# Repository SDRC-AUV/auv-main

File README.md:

auv-main
========

Central repository for documentation and useful links related to the AUV.

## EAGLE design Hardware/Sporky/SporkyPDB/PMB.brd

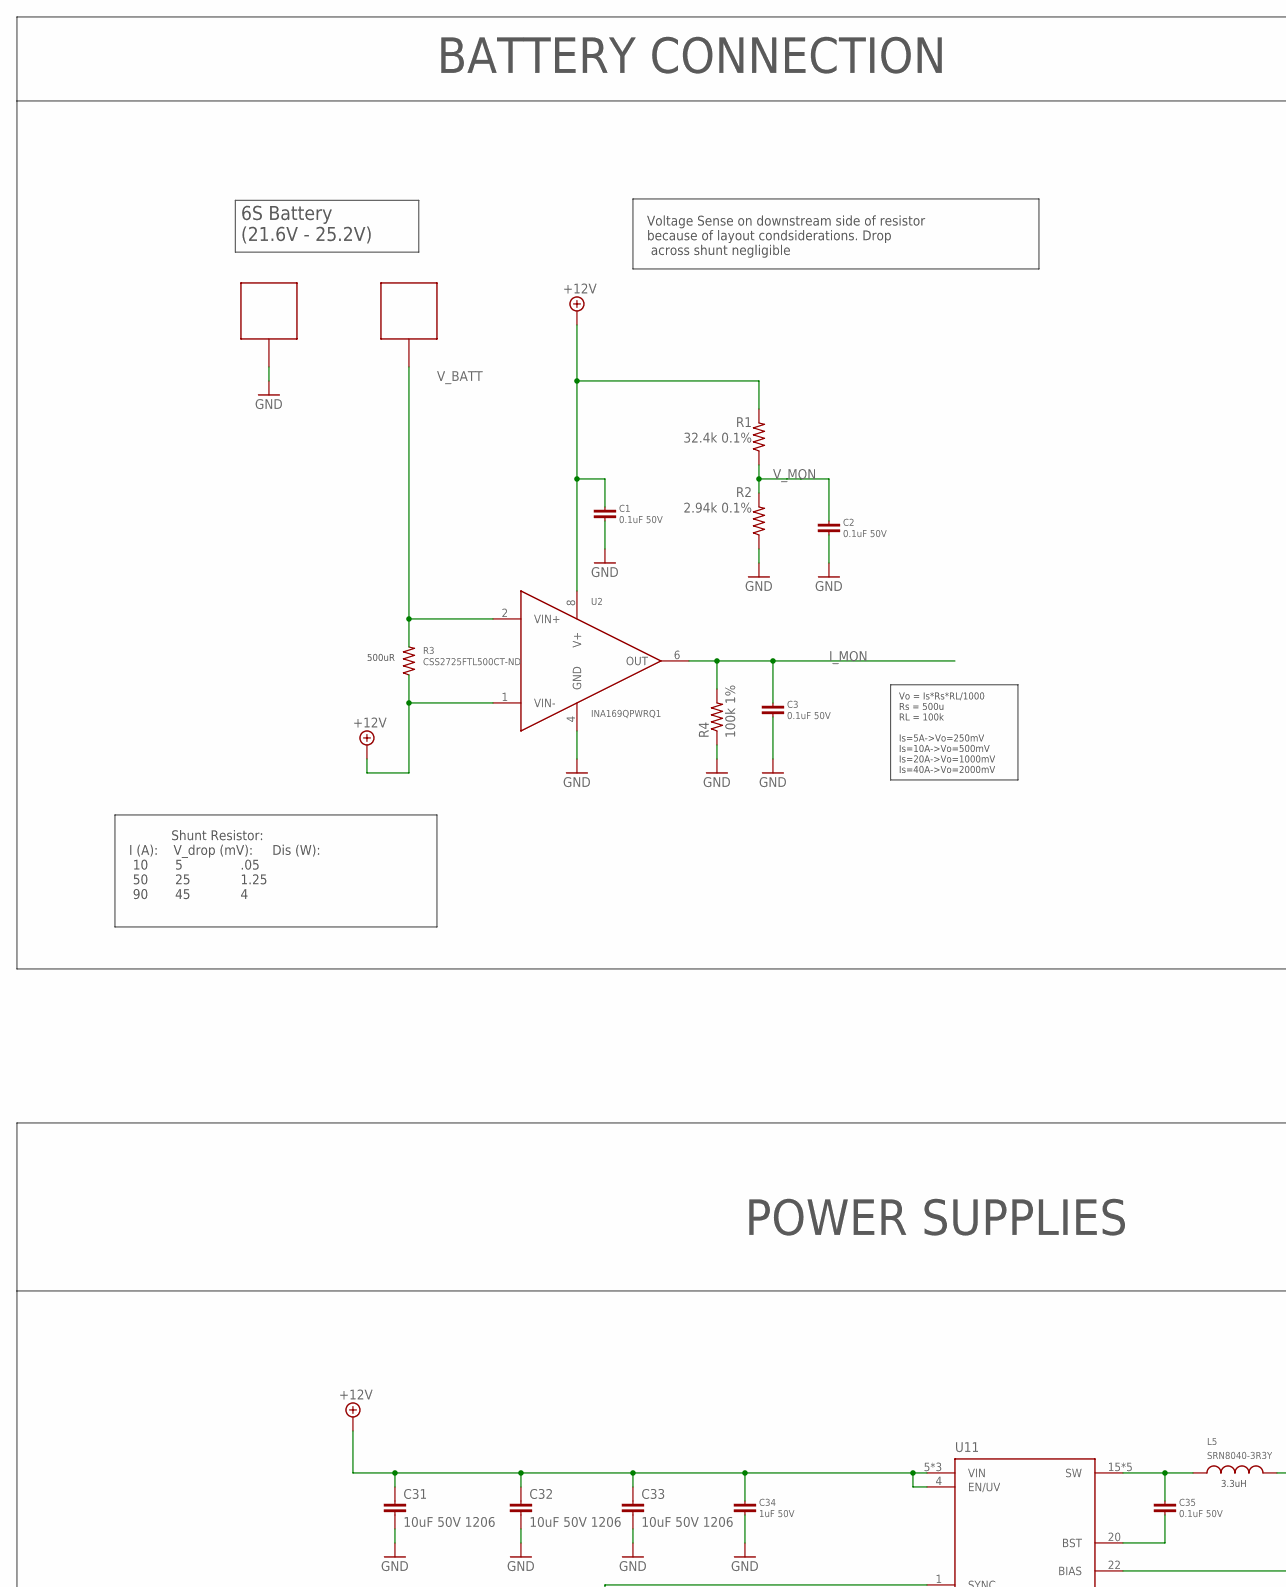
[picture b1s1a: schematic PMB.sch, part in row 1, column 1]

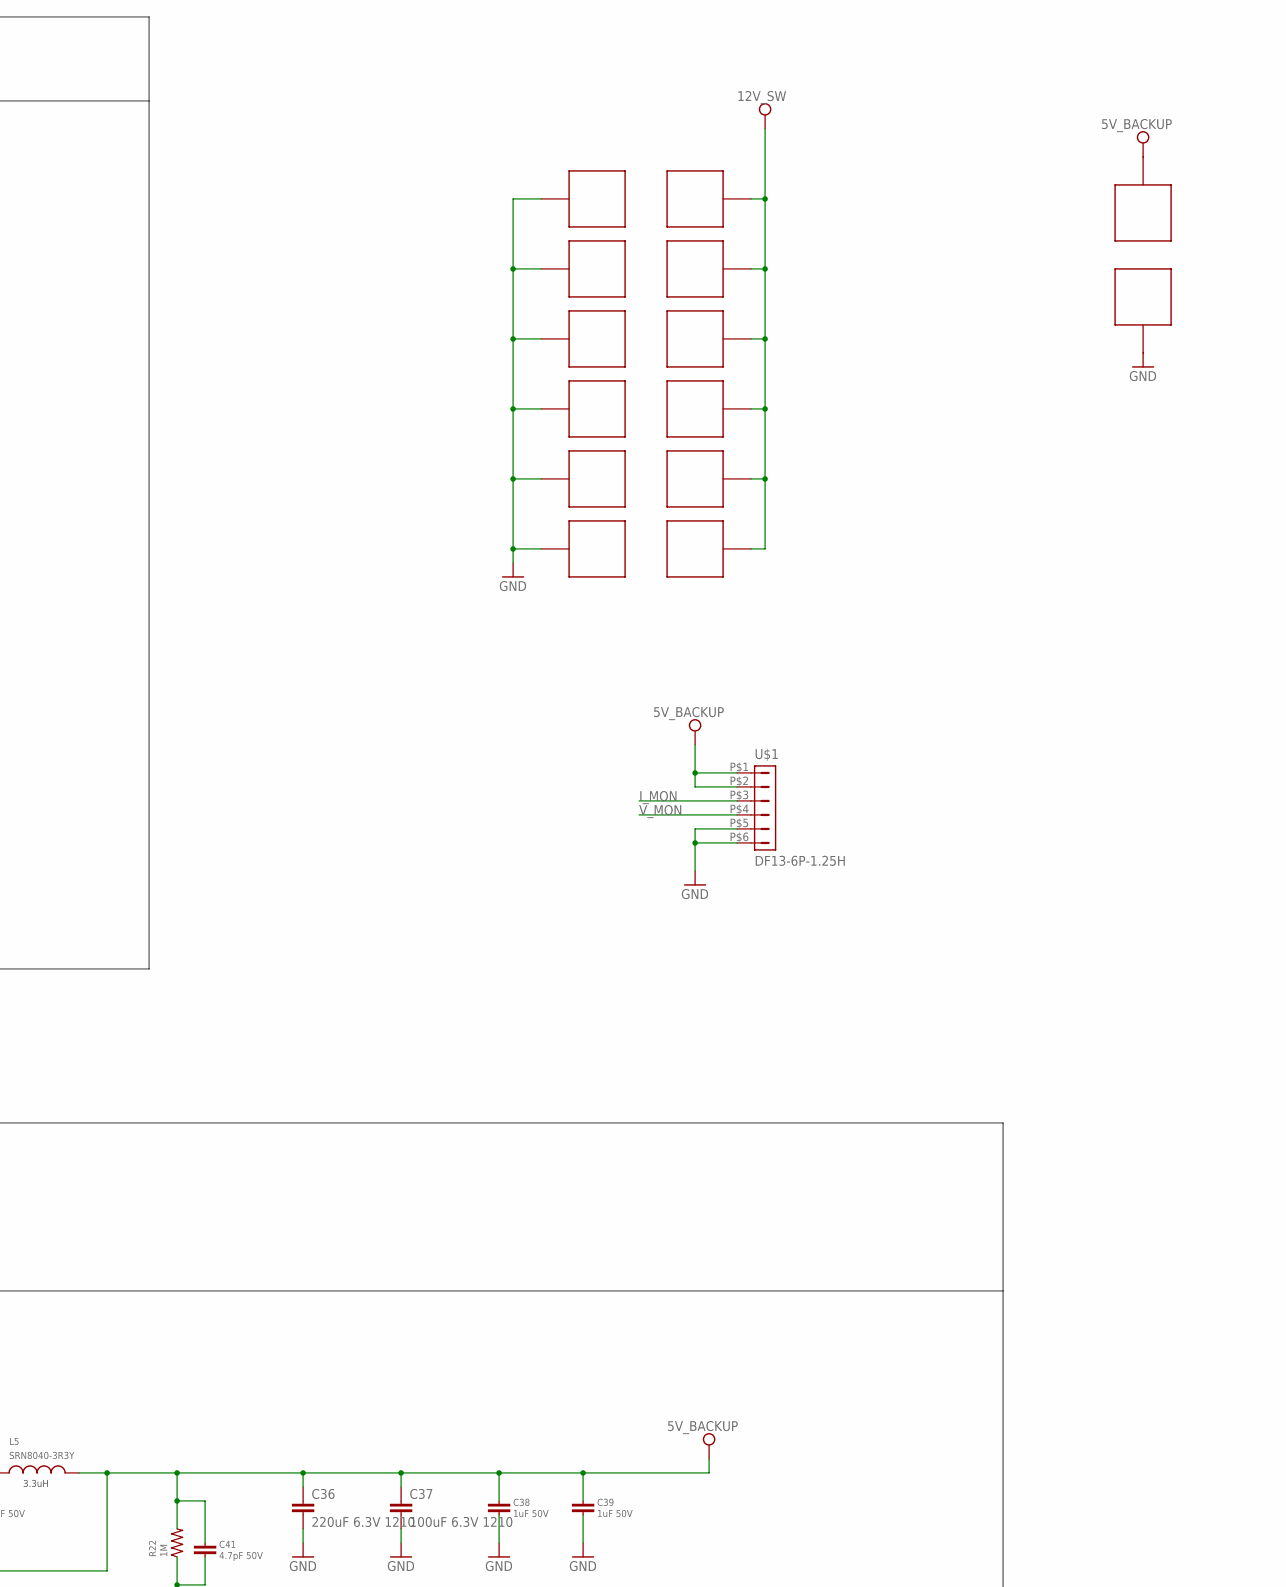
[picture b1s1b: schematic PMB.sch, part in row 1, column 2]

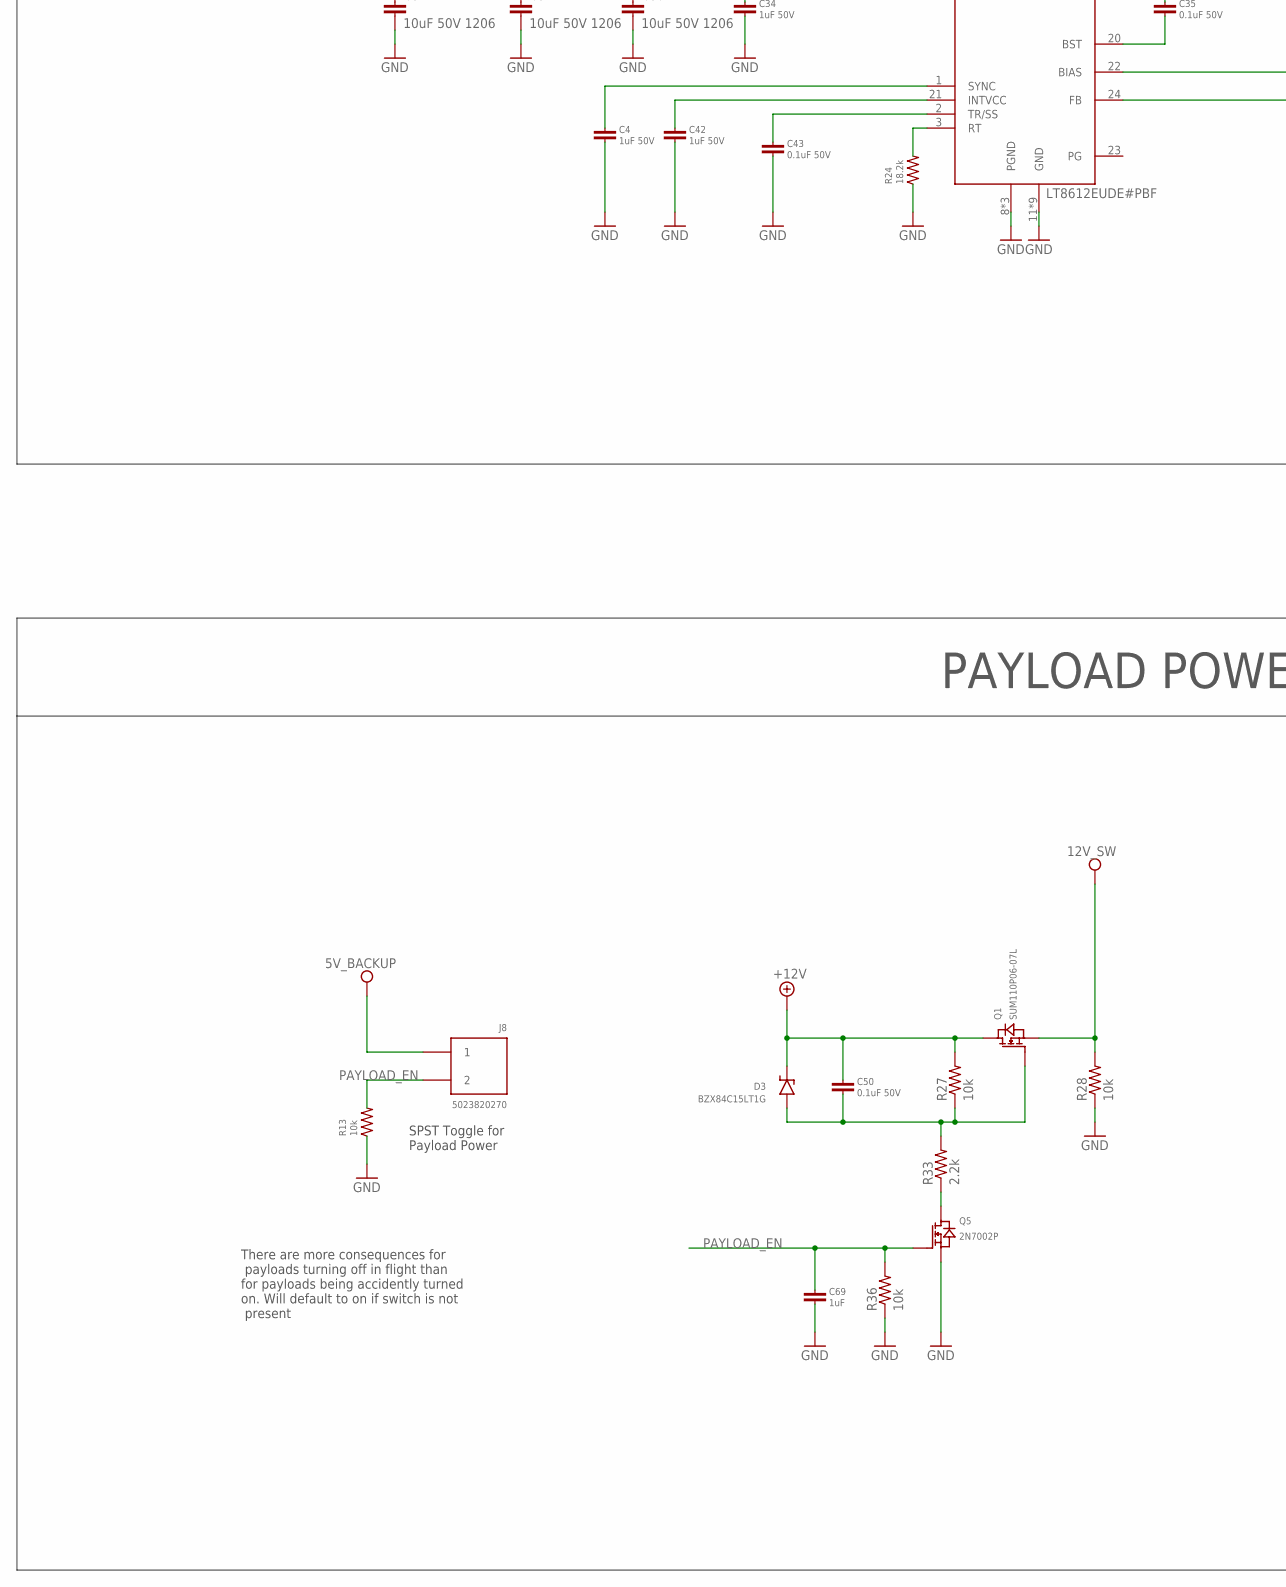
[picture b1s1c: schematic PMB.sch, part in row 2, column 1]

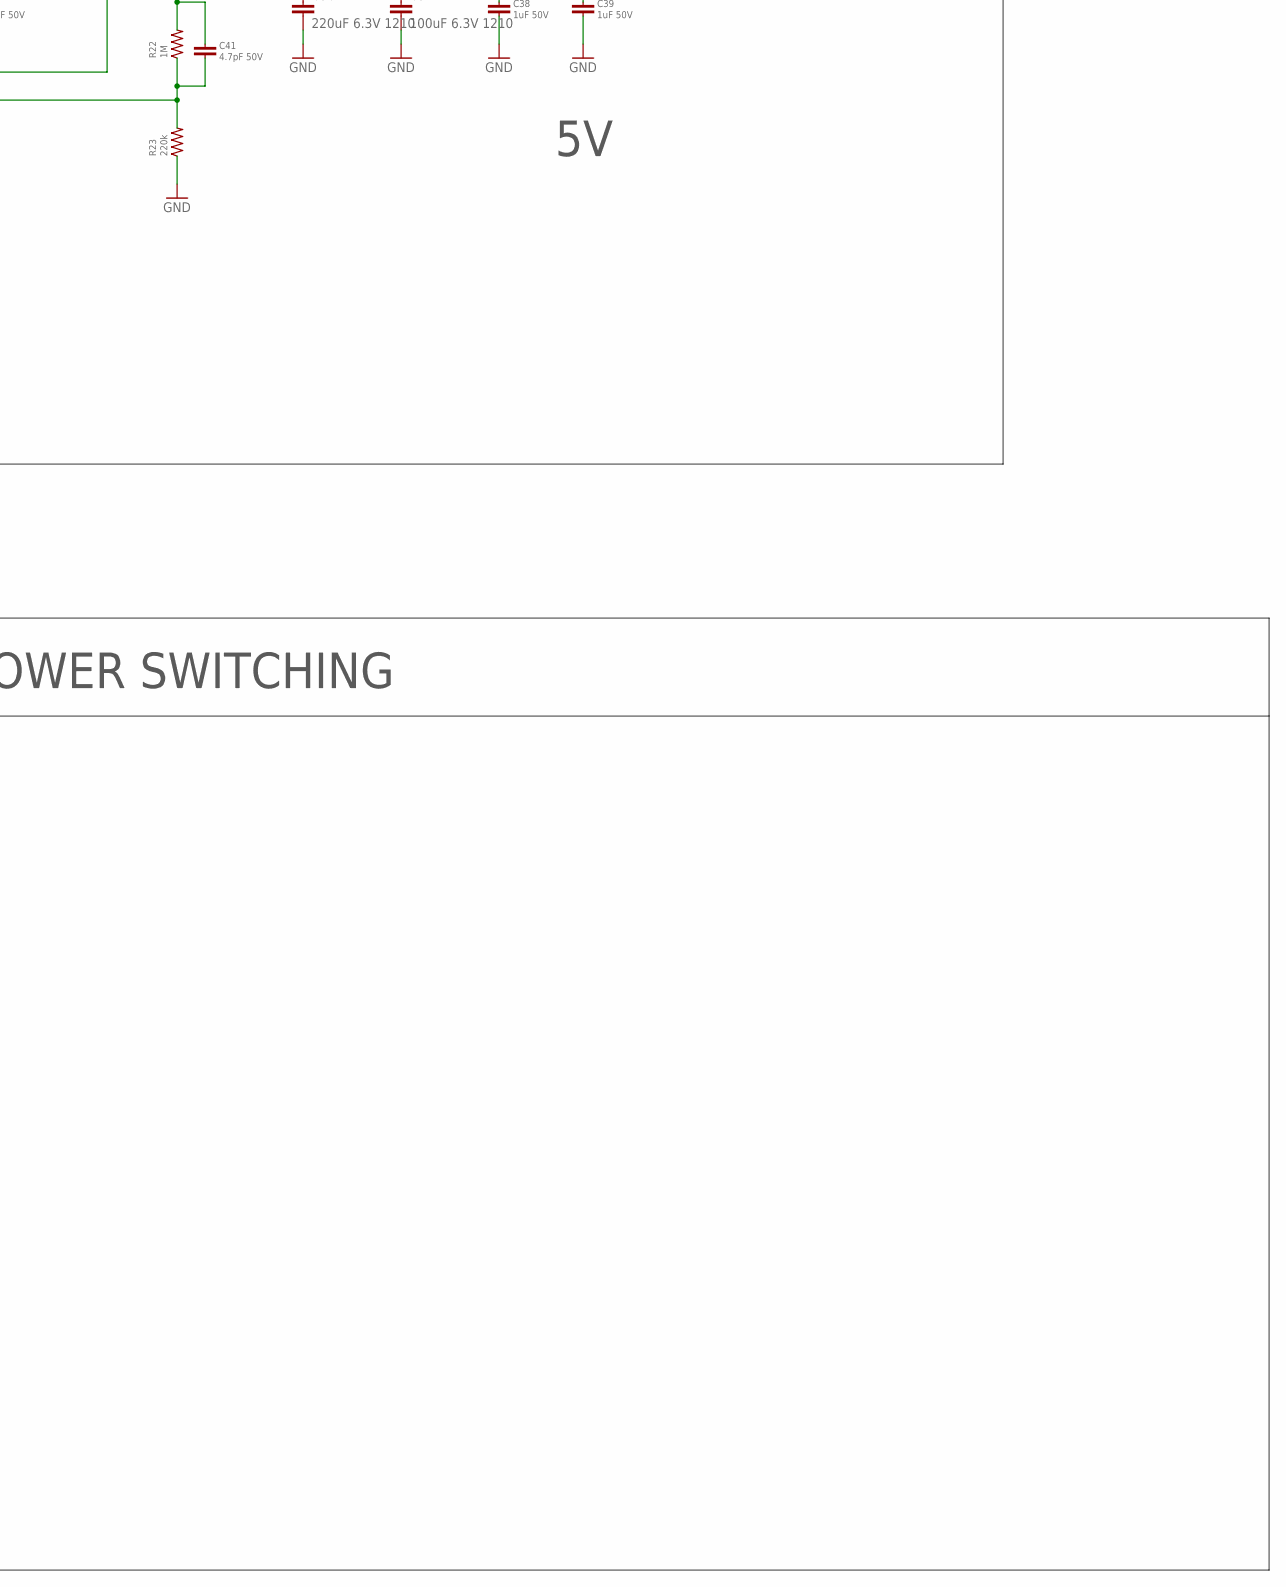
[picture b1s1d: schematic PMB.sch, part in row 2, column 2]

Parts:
C1, C2, C3, C35, C43, C50: 0.1uF 50V; 0805
C4, C34, C38, C39, C42: 1uF 50V; 0805
C31, C32, C33: 10uF 50V 1206; 1206
C36: 220uF 6.3V 1210; 1210
C37: 100uF 6.3V 1210; 1210
C41: 4.7pF 50V; 0805
C69: 1uF; 0805
D3: BZX84C15LT1G; SOT-23-3
J8: 5023820270; CLIK-MATE_1.25MM_2
L5: SRN8040-3R3Y; BOURNS_SRN8040
P1, P2: SOLDER_PAD_(1); SOLDER_PAD_10X5
P3, P5, P6, P8, P9, P10, P11, P12, P14, P16, P17, P18: SOLDER_PAD_(10); SOLDER_PAD_3X6
P13, P15: SOLDER_PAD_(15); SOLDER_PAD_2X4
Q1: SUM110P06-07L; TO-263-3_INFINEON
Q5: 2N7002P; SOT-23-3
R1: 32.4k 0.1%; R0805
R2: 2.94k 0.1%; R0805
R3: CSS2725FTL500CT-ND; 2725
R4: 100k 1%; R0805
R13: 10k; 0805
R22: 1M; 0805
R23: 220k; 0805
R24: 18.2k; 0805
R27, R28, R36: 10k; R0805
R33: 2.2k; R0805
U2: INA169QPWRQ1; TSSOP-8
U11: LT8612EUDE#PBF; WFQFN-28
U$1: DF13-6P-1.25H; DF13A-6P-1.25H

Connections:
5V_BACKUP: C36.1, C37.1, C38.1, C39.1, C41.1, J8.1, L5.2, P13.P$1, R22.2, U11.22 (BIAS), U$1.P$1 (1), U$1.P$2 (2)
12V_SW: P9.P$1, P10.P$1, P11.P$1, P12.P$1, P14.P$1, P18.P$1, Q1.3 (S), R28.2
+12V: C1.1, C31.1, C32.1, C33.1, C34.1, C50.1, D3.3 (C), Q1.2 (D), R1.2, R3.1, R27.2, U2.1 (VIN-), U2.8 (V+), U11.4 (EN/UV), U11.5 (VIN), U11.6 (VIN), U11.7 (VIN)
GND: C1.2, C2.2, C3.2, C4.2, C31.2, C32.2, C33.2, C34.2, C36.2, C37.2, C38.2, C39.2, C42.2, C43.2, C69.2, P1.1, P3.P$1, P5.P$1, P6.P$1, P8.P$1, P15.P$1, P16.P$1, P17.P$1, Q5.2 (S), R2.1, R4.1, R13.1, R23.1, R24.1, R28.1, R36.1, U2.4 (GND), U11.8 (PGND), U11.9 (PGND), U11.10 (PGND), U11.11 (GND), U11.12 (GND), U11.13 (GND), U11.14 (GND), U11.25 (GND), U11.26 (GND), U11.27 (GND), U11.28 (GND), U11.29 (GND), U$1.P$5 (5), U$1.P$6 (6)
I_MON: C3.1, R4.2, U2.6 (OUT), U$1.P$3 (3)
unnamed: C42.1, U11.21 (INTVCC)
unnamed: C43.1, U11.2 (TR/SS)
unnamed: R24.2, U11.3 (RT)
unnamed: C35.1, L5.1, U11.15 (SW), U11.16 (SW), U11.17 (SW), U11.18 (SW), U11.19 (SW)
unnamed: C35.2, U11.20 (BST)
unnamed: C41.2, R22.1, R23.2, U11.24 (FB)
unnamed: C4.1, U11.1 (SYNC)
unnamed: C50.2, D3.1 (A), Q1.1 (G), R27.1, R33.2
unnamed: Q5.3 (D), R33.1
PAYLOAD_EN: C69.1, J8.2, Q5.1 (G), R13.2, R36.2
V_BATT: P2.1, R3.2, U2.2 (VIN+)
V_MON: C2.1, R1.1, R2.2, U$1.P$4 (4)

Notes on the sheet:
POWER SUPPLIES
3.3uH
BATTERY CONNECTION
500uR
SPST Toggle for Payload Power
PAYLOAD POWER SWITCHING
There are more consequences for payloads turning off in flight than for payloads being accidently turned on. Will default to on if switch is not present
6S Battery (21.6V - 25.2V)
Vo = Is*Rs*RL/1000 Rs = 500u RL = 100k Is=5A->Vo=250mV Is=10A->Vo=500mV Is=20A->Vo=1000mV Is=40A->Vo=2000mV
Voltage Sense on downstream side of resistor because of layout condsiderations. Drop across shunt negligible
Shunt Resistor: I (A): V_drop (mV): Dis (W): 10 5 .05 50 25 1.25 90 45 4

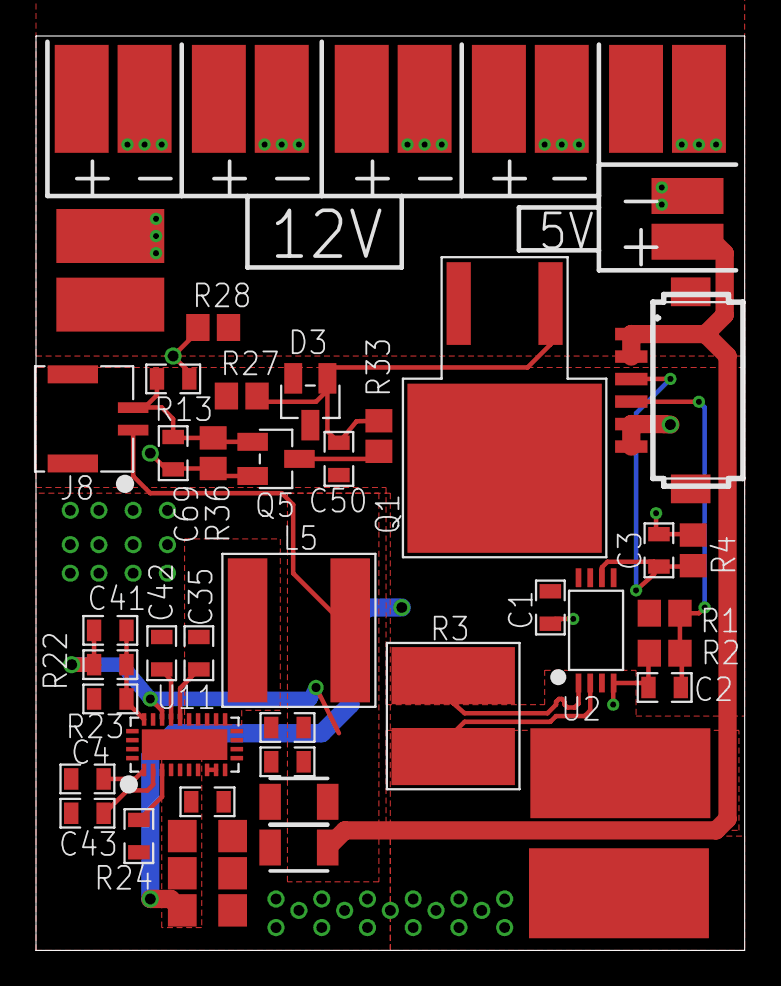
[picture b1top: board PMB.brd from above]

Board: 2 copper layers, 39.4 x 50.8 mm, 54 parts (0 on the bottom side), 17 nets.

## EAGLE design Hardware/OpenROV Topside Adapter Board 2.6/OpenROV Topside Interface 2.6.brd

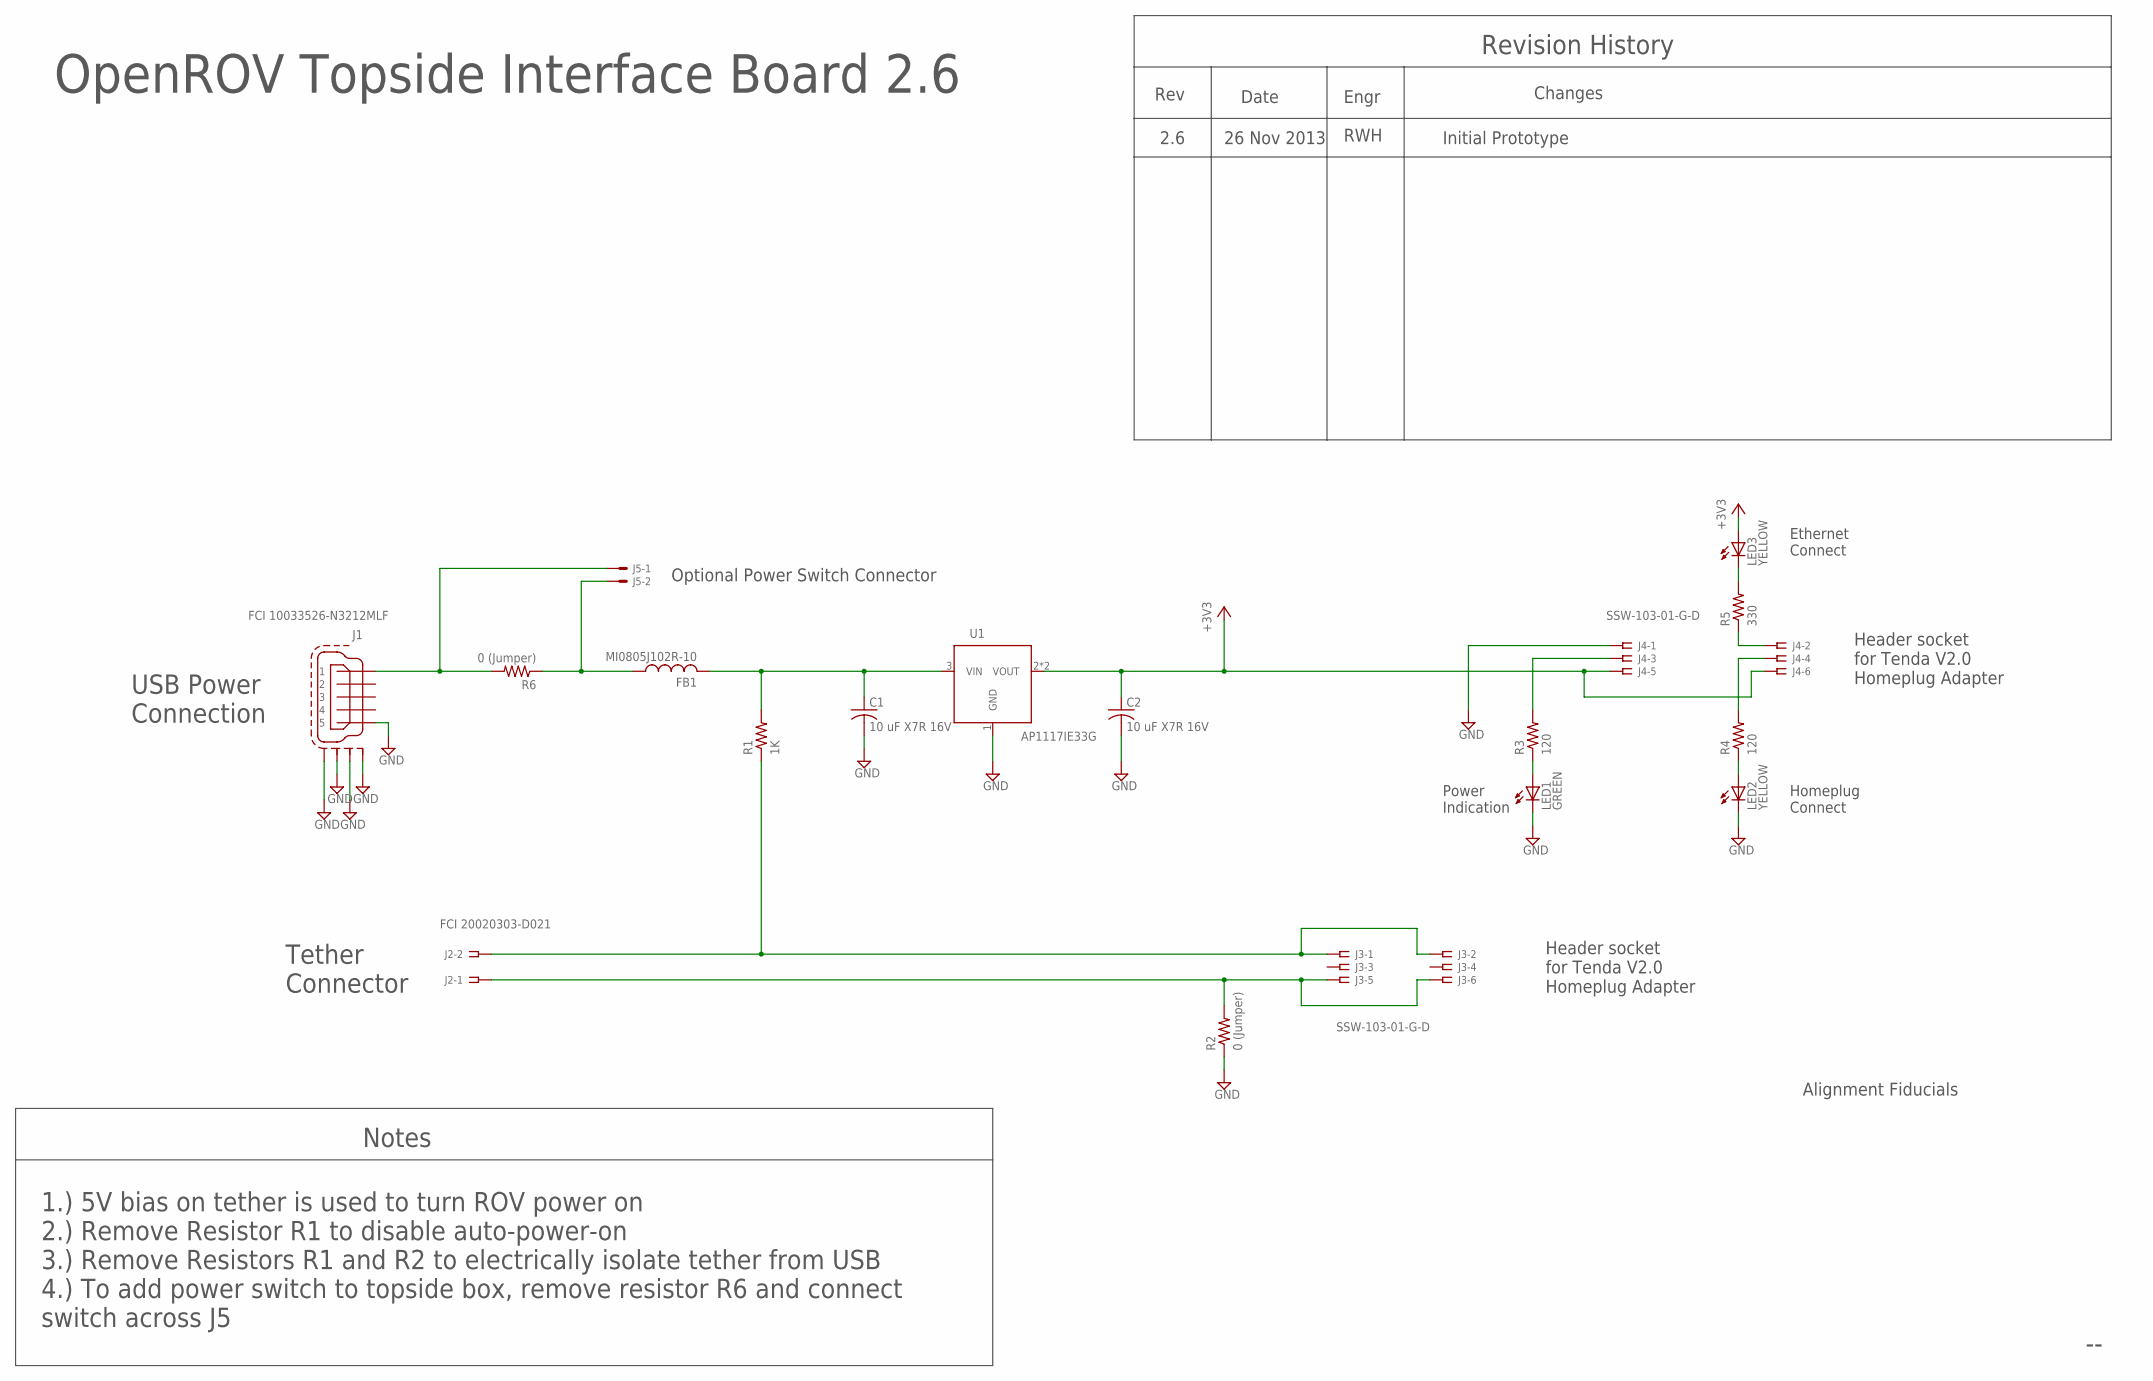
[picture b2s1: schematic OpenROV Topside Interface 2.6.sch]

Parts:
C1, C2: 10 uF X7R 16V; R1206
FB1: MI0805J102R-10; R0805
J1: FCI 10033526-N3212MLF; USB_MINI-B_SM
J2: FCI 20020303-D021; FCI_09-381_2PL
J3, J4: SSW-103-01-G-D; SSW-103-02-S-D
J5: HDR_1X2X0.100-ALT_SILK; 22-23-2021_ALT_SILK
LED1: GREEN; LED_0805_BOTTOM_MT(OSRAM)
LED2, LED3: YELLOW; LED_0805_BOTTOM_MT(OSRAM)
R1: 1K; R0805
R2, R6: 0 (Jumper); R0805
R3, R4: 120; R0805
R5: 330; R0805
U1: AP1117IE33G; SOT223

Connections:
+3V3: C2.1, J4.5, J4.6, LED3.A, U1.2 (VOUT), U1.4 (VOUT)
GND: C1.2, C2.2, J1.5, J1.M1 (S1), J1.M2 (S2), J1.M3 (S3), J1.M4 (S4), J4.1, LED1.C, LED2.C, R2.1, U1.1 (GND)
unnamed: J2.1A, J2.1B, J3.5, J3.6, R2.2
unnamed: J2.2A, J2.2B, J3.1, J3.2, R1.1
unnamed: J1.1, J5.1, R6.2
unnamed: C1.1, FB1.2, R1.2, U1.3 (VIN)
unnamed: LED3.C, R5.2
unnamed: J4.3, R3.2
unnamed: LED1.A, R3.1
unnamed: LED2.A, R4.1
unnamed: J4.4, R4.2
unnamed: FB1.1, J5.2, R6.1
unnamed: J4.2, R5.1

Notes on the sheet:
Revision History
Rev
Date
Changes
2.6
26 Nov 2013
Initial Prototype
Engr
RWH
OpenROV Topside Interface Board 2.6
Tether Connector
USB Power Connection
Header socket for Tenda V2.0 Homeplug Adapter
Power Indication
Homeplug Connect
Ethernet Connect
Notes
1.) 5V bias on tether is used to turn ROV power on 2.) Remove Resistor R1 to disable auto-power-on 3.) Remove Resistors R1 and R2 to electrically isolate tether from USB 4.) To add power switch to topside box, remove resistor R6 and connect switch across J5
Alignment Fiducials
Optional Power Switch Connector

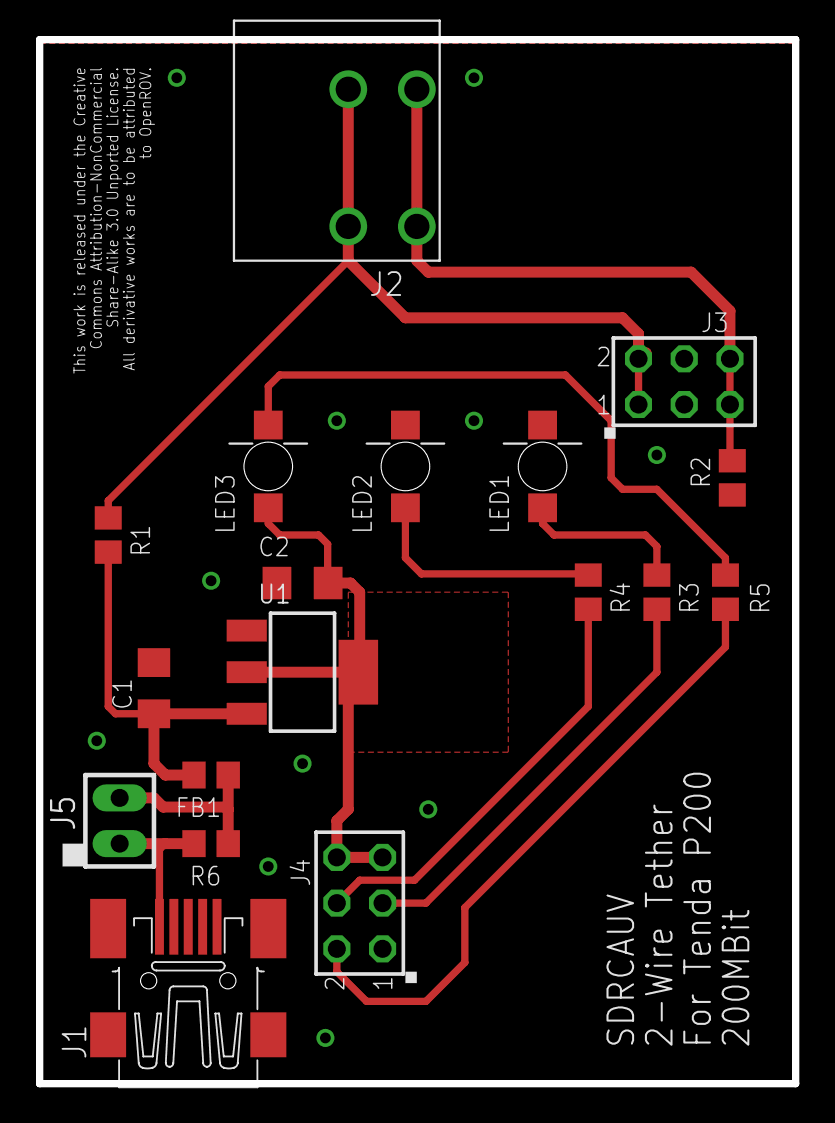
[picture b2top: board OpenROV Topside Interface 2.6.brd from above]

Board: 2 copper layers, 42.0 x 58.0 mm, 18 parts (0 on the bottom side), 13 nets.

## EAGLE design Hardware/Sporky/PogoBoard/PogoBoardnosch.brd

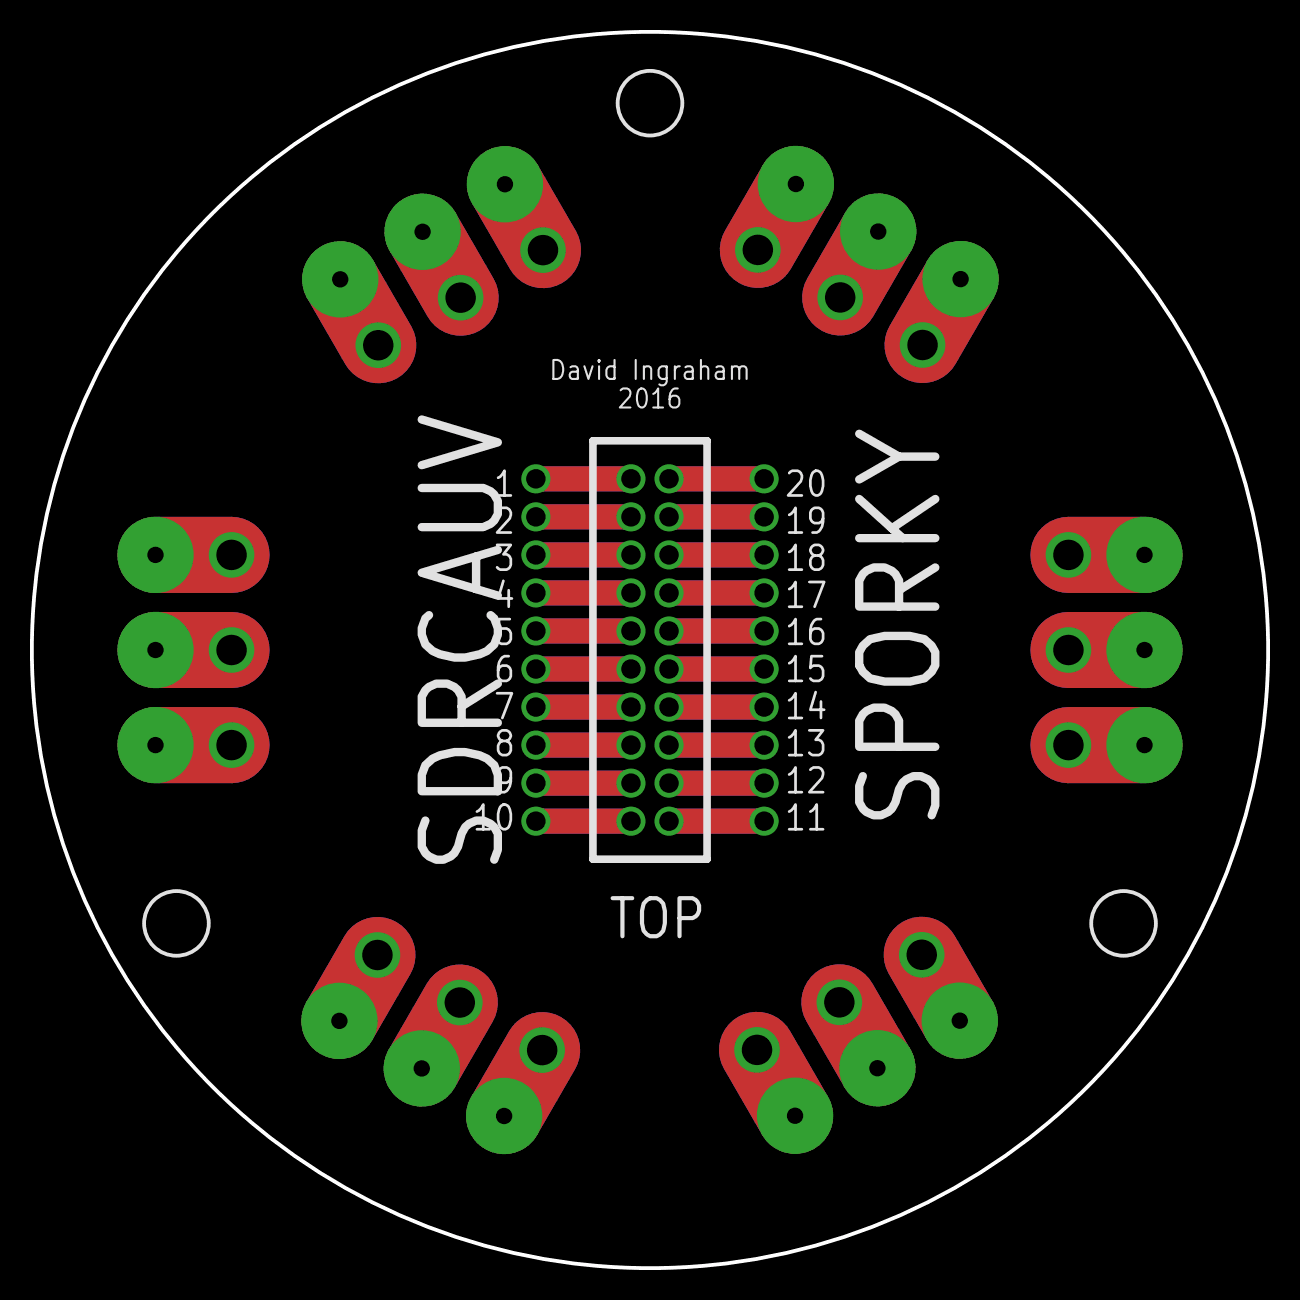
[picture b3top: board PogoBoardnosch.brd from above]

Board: 2 copper layers, 82.5 x 82.5 mm, 22 parts (0 on the bottom side), 3 nets.

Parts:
E$1, E$2, E$3, E$4, E$5, E$6, E$7, E$8, E$9, E$10, E$11, E$12: SPRING_PIN_5MM
E$13, E$14, E$15, E$16: CON_100MIL_10
S$1, S$2, S$3, S$4, S$5, S$6: SPRING_PIN_5MM

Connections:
S$19: E$13.1, E$16.1
S$20: E$13.2, E$16.2
S$22: E$13.3, E$16.3

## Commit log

2016-02-12 added link to ROS documentation
2016-02-12 added links to competition documentation
2016-02-16 Created Meeting Minutes folder
2016-04-01 Parameters: Added default parameters for Triton from QGC
2016-04-03 Hardware: Uploaded Interface board and Sporky Custom hardware
2016-04-18 Parms: upload newer Triton Parameter Set
2016-05-04 Parms: Correct motor reverse for new motor mapping
2016-06-12 PARMS: Added new Parameters for Triton

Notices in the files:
parts and their libraries:
OpenROV General Library: This work is released under the Creative Commons
Attribution-NonCommercial-Share Alike 3.0
SparkFun-Capacitors: Licensing: CC v3.0 Share-Alike You are welcome to use this library for commercial purposes.
